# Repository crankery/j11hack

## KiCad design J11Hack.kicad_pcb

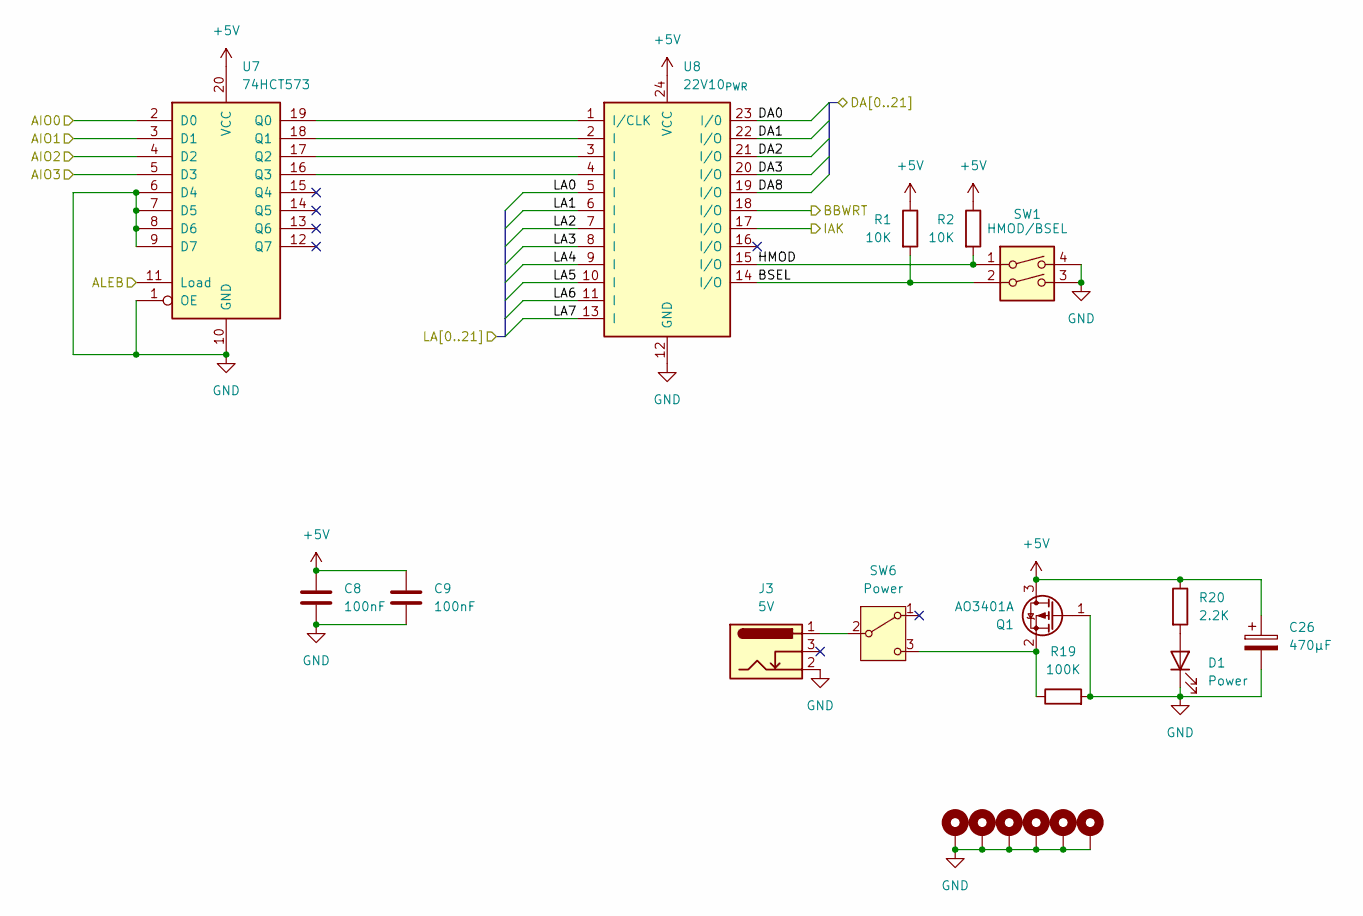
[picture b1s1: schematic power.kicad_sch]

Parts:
C8, C9: 100nF; C_Disc_D4.3mm_W1.9mm_P5.00mm
C26: 470µF; CP_Radial_D8.0mm_P3.50mm
D1: Power; LED_D3.0mm
H1, H2, H3, H4, H5, H6: MountingHole_Pad; MountingHole_2.7mm_M2.5_DIN965_Pad
J3: 5V; BarrelJack_Horizontal
Q1: AO3401A; SOT-23
R1, R2: 10K; R_Axial_DIN0207_L6.3mm_D2.5mm_P7.62mm_Horizontal
R19: 100K; R_Axial_DIN0207_L6.3mm_D2.5mm_P7.62mm_Horizontal
R20: 2.2K; R_Axial_DIN0207_L6.3mm_D2.5mm_P7.62mm_Horizontal
SW1: HMOD/BSEL; SW_DIP_SPSTx02_Slide_9.78x7.26mm_W7.62mm_P2.54mm
SW6: Power; SW_2AS1T2A1M6QES
U7: 74HCT573; DIP-20_W7.62mm_Socket
U8: 22V10_{PWR}; DIP-24_W7.62mm_Socket

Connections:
+5V: C8.1, C9.1, C26.1, Q1.3 (D), R1.1, R2.1, R20.1, U7.20 (VCC), U8.24 (VCC); also elsewhere on the board
/CPU/AIO0: U7.2 (D0); also elsewhere on the board
/CPU/AIO1: U7.3 (D1); also elsewhere on the board
/CPU/AIO2: U7.4 (D2); also elsewhere on the board
/CPU/AIO3: U7.5 (D3); also elsewhere on the board
/CPU/ALEB: U7.11 (Load); also elsewhere on the board
/CPU/BBWRT: U8.18 (I/O); also elsewhere on the board
/CPU/DA0: U8.23 (I/0); also elsewhere on the board
/CPU/DA1: U8.22 (I/O); also elsewhere on the board
/CPU/DA2: U8.21 (I/O); also elsewhere on the board
/CPU/DA3: U8.20 (I/O); also elsewhere on the board
/CPU/DA8: U8.19 (I/O); also elsewhere on the board
/CPU/LA0: U8.5 (I); also elsewhere on the board
/CPU/LA1: U8.6 (I); also elsewhere on the board
/CPU/LA2: U8.7 (I); also elsewhere on the board
/CPU/LA3: U8.8 (I); also elsewhere on the board
/CPU/LA4: U8.9 (I); also elsewhere on the board
/CPU/LA5: U8.10 (I); also elsewhere on the board
/CPU/LA6: U8.11 (I); also elsewhere on the board
/CPU/LA7: U8.13 (I); also elsewhere on the board
/Power/BSEL: R1.2, SW1.2, U8.14 (I/O)
/Power/HMOD: R2.2, SW1.1, U8.15 (I/O)
/Power/IAK: U8.17 (I/O)
GND: C8.2, C9.2, C26.2, D1.1 (K), H1.1 (1_1), H2.1 (1_1), H3.1 (1_1), H4.1 (1_1), H5.1 (1_1), H6.1 (1_1), J3.2, Q1.1 (G), R19.2, SW1.3, SW1.4, U7.1 (OE), U7.6 (D4), U7.7 (D5), U7.8 (D6), U7.9 (D7), U7.10 (GND), U8.12 (GND); also elsewhere on the board
unnamed: D1.2 (A), R20.2
unnamed: Q1.2 (S), R19.1, SW6.3 (C)
unnamed: J3.1, SW6.2 (B)
unnamed: U7.19 (Q0), U8.1 (I/CLK)
unnamed: U7.18 (Q1), U8.2 (I)
unnamed: U7.17 (Q2), U8.3 (I)
unnamed: U7.16 (Q3), U8.4 (I)

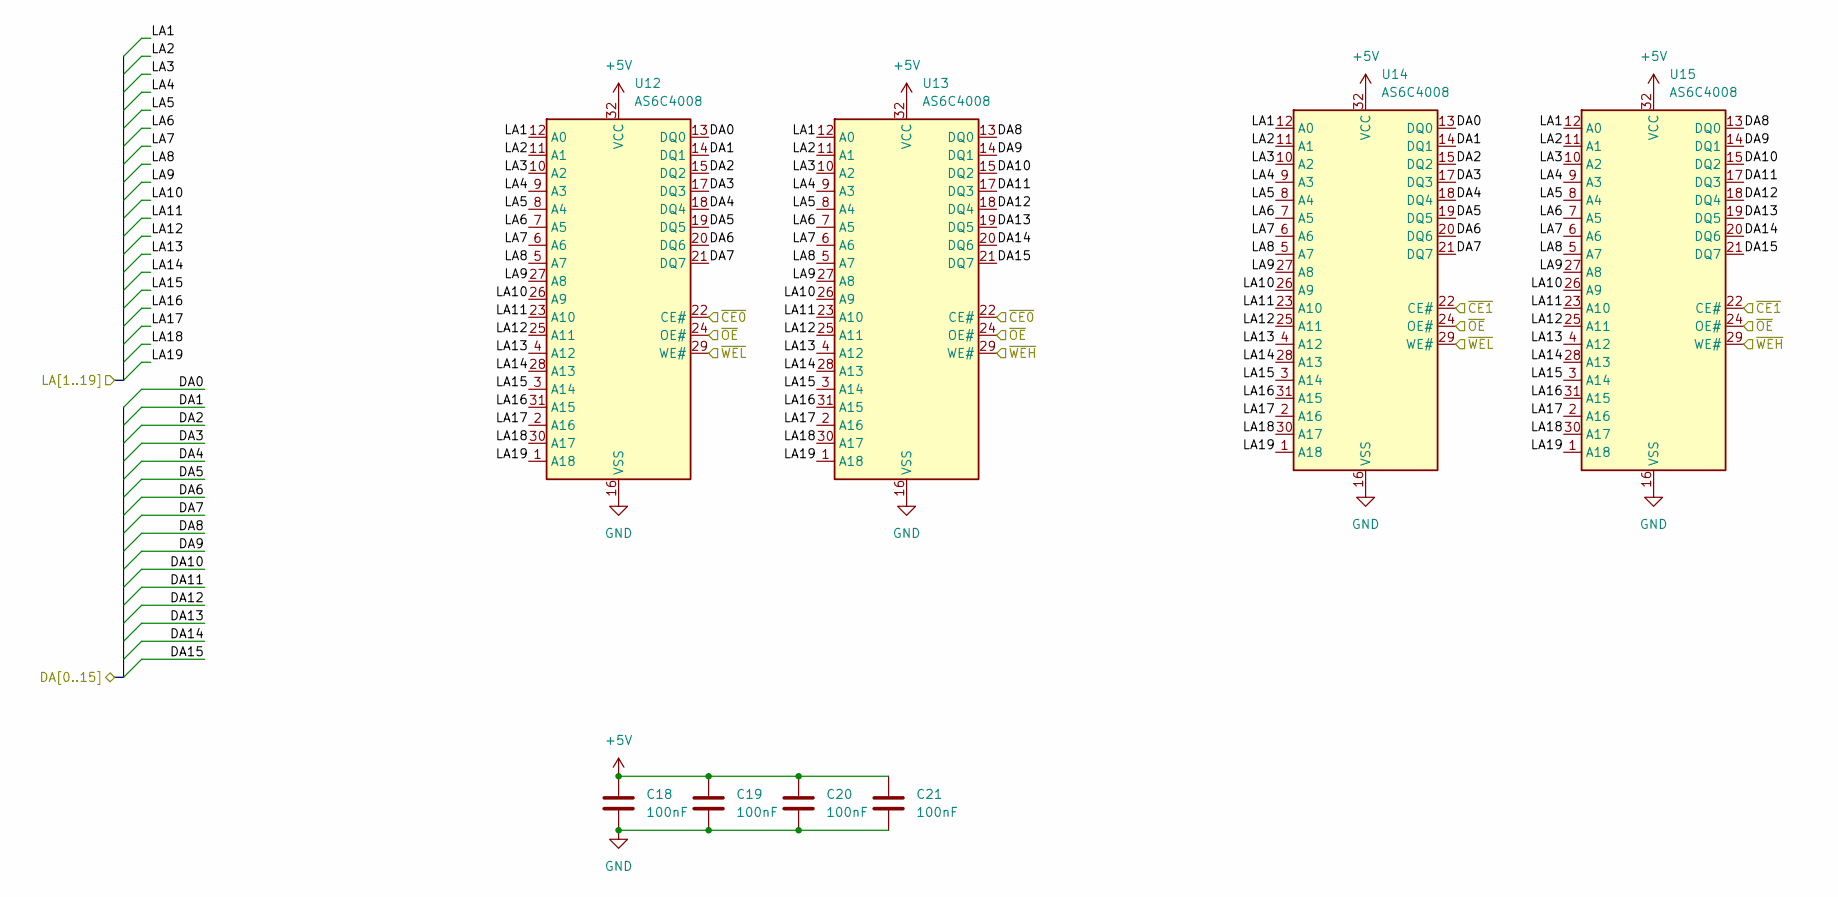
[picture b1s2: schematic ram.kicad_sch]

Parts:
C18, C19, C20, C21: 100nF; C_Disc_D4.3mm_W1.9mm_P5.00mm
U12, U13, U14, U15: AS6C4008; DIP-32_W15.24mm_Socket

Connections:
+5V: C18.1, C19.1, C20.1, C21.1, U12.32 (VCC), U13.32 (VCC), U14.32 (VCC), U15.32 (VCC); also elsewhere on the board
/CPU/DA0: U12.13 (DQ0), U14.13 (DQ0); also elsewhere on the board
/CPU/DA1: U12.14 (DQ1), U14.14 (DQ1); also elsewhere on the board
/CPU/DA2: U12.15 (DQ2), U14.15 (DQ2); also elsewhere on the board
/CPU/DA3: U12.17 (DQ3), U14.17 (DQ3); also elsewhere on the board
/CPU/DA4: U12.18 (DQ4), U14.18 (DQ4); also elsewhere on the board
/CPU/DA5: U12.19 (DQ5), U14.19 (DQ5); also elsewhere on the board
/CPU/DA6: U12.20 (DQ6), U14.20 (DQ6); also elsewhere on the board
/CPU/DA7: U12.21 (DQ7), U14.21 (DQ7); also elsewhere on the board
/CPU/DA8: U13.13 (DQ0), U15.13 (DQ0); also elsewhere on the board
/CPU/DA9: U13.14 (DQ1), U15.14 (DQ1); also elsewhere on the board
/CPU/DA10: U13.15 (DQ2), U15.15 (DQ2); also elsewhere on the board
/CPU/DA11: U13.17 (DQ3), U15.17 (DQ3); also elsewhere on the board
/CPU/DA12: U13.18 (DQ4), U15.18 (DQ4); also elsewhere on the board
/CPU/DA13: U13.19 (DQ5), U15.19 (DQ5); also elsewhere on the board
/CPU/DA14: U13.20 (DQ6), U15.20 (DQ6); also elsewhere on the board
/CPU/DA15: U13.21 (DQ7), U15.21 (DQ7); also elsewhere on the board
/CPU/LA0: U12.12 (A0), U13.12 (A0), U14.12 (A0), U15.12 (A0); also elsewhere on the board
/CPU/LA1: U12.11 (A1), U13.11 (A1), U14.11 (A1), U15.11 (A1); also elsewhere on the board
/CPU/LA2: U12.10 (A2), U13.10 (A2), U14.10 (A2), U15.10 (A2); also elsewhere on the board
/CPU/LA3: U12.9 (A3), U13.9 (A3), U14.9 (A3), U15.9 (A3); also elsewhere on the board
/CPU/LA4: U12.8 (A4), U13.8 (A4), U14.8 (A4), U15.8 (A4); also elsewhere on the board
/CPU/LA5: U12.7 (A5), U13.7 (A5), U14.7 (A5), U15.7 (A5); also elsewhere on the board
/CPU/LA6: U12.6 (A6), U13.6 (A6), U14.6 (A6), U15.6 (A6); also elsewhere on the board
/CPU/LA7: U12.5 (A7), U13.5 (A7), U14.5 (A7), U15.5 (A7); also elsewhere on the board
/CPU/LA8: U12.27 (A8), U13.27 (A8), U14.27 (A8), U15.27 (A8); also elsewhere on the board
/CPU/LA9: U12.26 (A9), U13.26 (A9), U14.26 (A9), U15.26 (A9); also elsewhere on the board
/CPU/LA10: U12.23 (A10), U13.23 (A10), U14.23 (A10), U15.23 (A10); also elsewhere on the board
/CPU/LA11: U12.25 (A11), U13.25 (A11), U14.25 (A11), U15.25 (A11); also elsewhere on the board
/CPU/LA12: U12.4 (A12), U13.4 (A12), U14.4 (A12), U15.4 (A12); also elsewhere on the board
/CPU/LA13: U12.28 (A13), U13.28 (A13), U14.28 (A13), U15.28 (A13); also elsewhere on the board
/CPU/LA14: U12.3 (A14), U13.3 (A14), U14.3 (A14), U15.3 (A14); also elsewhere on the board
/CPU/LA15: U12.31 (A15), U13.31 (A15), U14.31 (A15), U15.31 (A15); also elsewhere on the board
/CPU/LA16: U12.2 (A16), U13.2 (A16), U14.2 (A16), U15.2 (A16); also elsewhere on the board
/CPU/LA17: U12.30 (A17), U13.30 (A17), U14.30 (A17), U15.30 (A17); also elsewhere on the board
/CPU/LA18: U12.1 (A18), U13.1 (A18), U14.1 (A18), U15.1 (A18); also elsewhere on the board
/CPU/~CE0: U12.22 (CE#), U13.22 (CE#); also elsewhere on the board
/CPU/~CE1: U14.22 (CE#), U15.22 (CE#); also elsewhere on the board
/CPU/~OE: U12.24 (OE#), U13.24 (OE#), U14.24 (OE#), U15.24 (OE#); also elsewhere on the board
/CPU/~WEH: U13.29 (WE#), U15.29 (WE#); also elsewhere on the board
/CPU/~WEL: U12.29 (WE#), U14.29 (WE#); also elsewhere on the board
GND: C18.2, C19.2, C20.2, C21.2, U12.16 (VSS), U13.16 (VSS), U14.16 (VSS), U15.16 (VSS); also elsewhere on the board

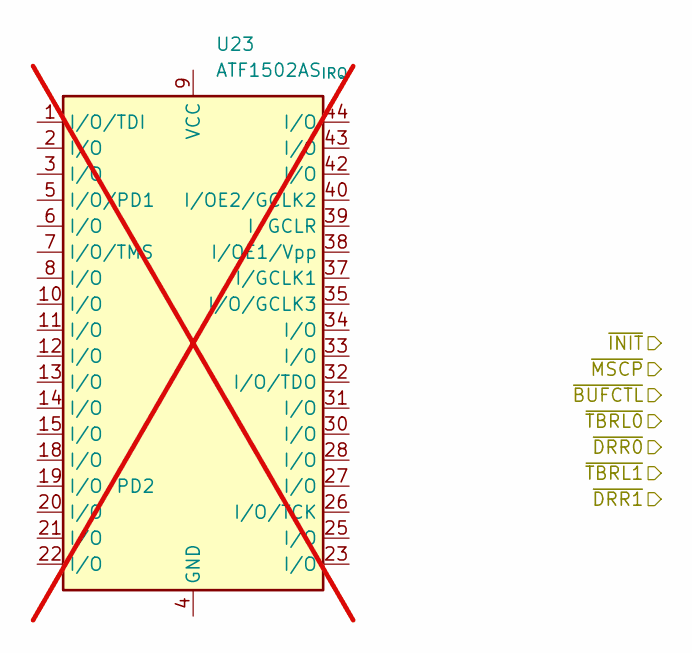
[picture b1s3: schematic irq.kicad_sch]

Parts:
U23: ATF1502AS_{IRQ}; TQFP-44_10x10mm_P0.8mm; not fitted

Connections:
unnamed: U23.4 (GND), U23.16 (GND), U23.24 (GND), U23.36 (GND)
unnamed: U23.9 (VCC), U23.17 (VCC), U23.29 (VCC), U23.41 (VCC)

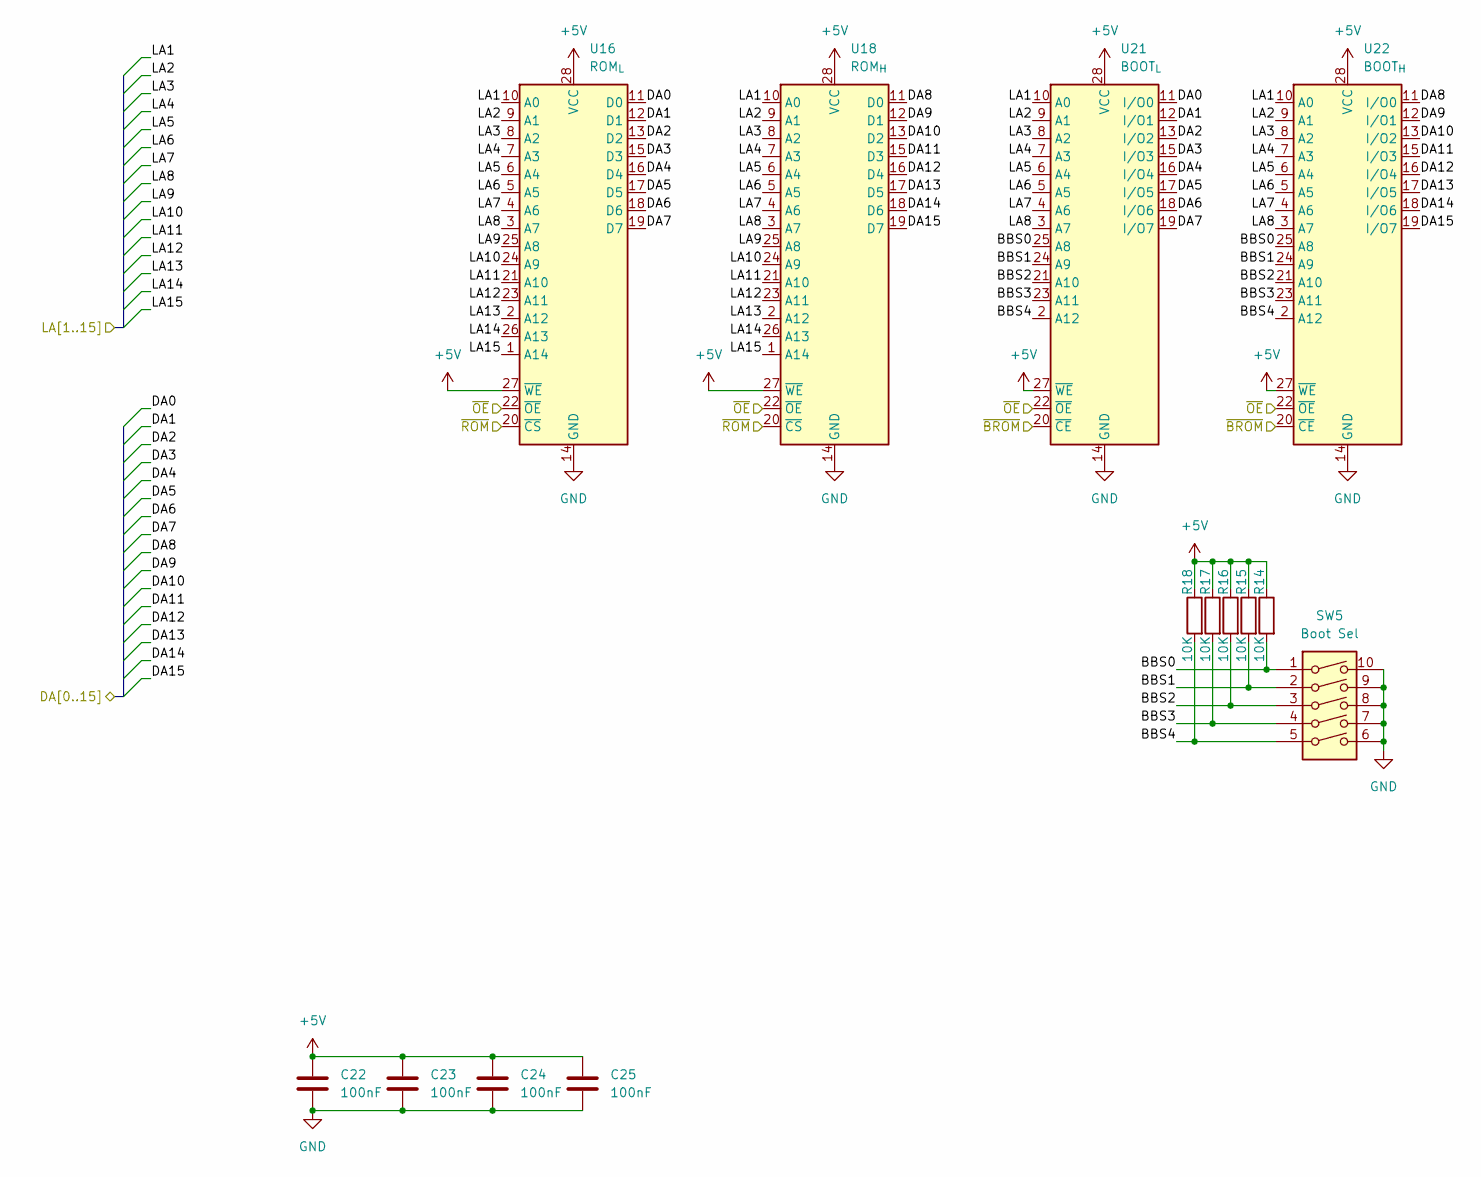
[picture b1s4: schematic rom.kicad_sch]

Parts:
C22, C23, C24, C25: 100nF; C_Disc_D4.3mm_W1.9mm_P5.00mm
R14, R15, R16, R17, R18: 10K; R_Axial_DIN0207_L6.3mm_D2.5mm_P7.62mm_Horizontal
SW5: Boot Sel; SW_DIP_SPSTx05_Slide_9.78x14.88mm_W7.62mm_P2.54mm
U16: ROM_{L}; DIP-28_W15.24mm_Socket
U18: ROM_{H}; DIP-28_W15.24mm_Socket
U21: BOOT_{L}; DIP-28_W15.24mm_Socket
U22: BOOT_{H}; DIP-28_W15.24mm_Socket

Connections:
+5V: C22.1, C23.1, C24.1, C25.1, R14.1, R15.1, R16.1, R17.1, R18.1, U16.27 (~WE), U16.28 (VCC), U18.27 (~WE), U18.28 (VCC), U21.27 (~WE), U21.28 (VCC), U22.27 (~WE), U22.28 (VCC); also elsewhere on the board
/CPU/DA0: U16.11 (D0), U21.11 (I/O0); also elsewhere on the board
/CPU/DA1: U16.12 (D1), U21.12 (I/O1); also elsewhere on the board
/CPU/DA2: U16.13 (D2), U21.13 (I/O2); also elsewhere on the board
/CPU/DA3: U16.15 (D3), U21.15 (I/O3); also elsewhere on the board
/CPU/DA4: U16.16 (D4), U21.16 (I/O4); also elsewhere on the board
/CPU/DA5: U16.17 (D5), U21.17 (I/O5); also elsewhere on the board
/CPU/DA6: U16.18 (D6), U21.18 (I/O6); also elsewhere on the board
/CPU/DA7: U16.19 (D7), U21.19 (I/O7); also elsewhere on the board
/CPU/DA8: U18.11 (D0), U22.11 (I/O0); also elsewhere on the board
/CPU/DA9: U18.12 (D1), U22.12 (I/O1); also elsewhere on the board
/CPU/DA10: U18.13 (D2), U22.13 (I/O2); also elsewhere on the board
/CPU/DA11: U18.15 (D3), U22.15 (I/O3); also elsewhere on the board
/CPU/DA12: U18.16 (D4), U22.16 (I/O4); also elsewhere on the board
/CPU/DA13: U18.17 (D5), U22.17 (I/O5); also elsewhere on the board
/CPU/DA14: U18.18 (D6), U22.18 (I/O6); also elsewhere on the board
/CPU/DA15: U18.19 (D7), U22.19 (I/O7); also elsewhere on the board
/CPU/LA0: U16.10 (A0), U18.10 (A0), U21.10 (A0), U22.10 (A0); also elsewhere on the board
/CPU/LA1: U16.9 (A1), U18.9 (A1), U21.9 (A1), U22.9 (A1); also elsewhere on the board
/CPU/LA2: U16.8 (A2), U18.8 (A2), U21.8 (A2), U22.8 (A2); also elsewhere on the board
/CPU/LA3: U16.7 (A3), U18.7 (A3), U21.7 (A3), U22.7 (A3); also elsewhere on the board
/CPU/LA4: U16.6 (A4), U18.6 (A4), U21.6 (A4), U22.6 (A4); also elsewhere on the board
/CPU/LA5: U16.5 (A5), U18.5 (A5), U21.5 (A5), U22.5 (A5); also elsewhere on the board
/CPU/LA6: U16.4 (A6), U18.4 (A6), U21.4 (A6), U22.4 (A6); also elsewhere on the board
/CPU/LA7: U16.3 (A7), U18.3 (A7), U21.3 (A7), U22.3 (A7); also elsewhere on the board
/CPU/LA8: U16.25 (A8), U18.25 (A8); also elsewhere on the board
/CPU/LA9: U16.24 (A9), U18.24 (A9); also elsewhere on the board
/CPU/LA10: U16.21 (A10), U18.21 (A10); also elsewhere on the board
/CPU/LA11: U16.23 (A11), U18.23 (A11); also elsewhere on the board
/CPU/LA12: U16.2 (A12), U18.2 (A12); also elsewhere on the board
/CPU/LA13: U16.26 (A13), U18.26 (A13); also elsewhere on the board
/CPU/LA14: U16.1 (A14), U18.1 (A14); also elsewhere on the board
/CPU/~BROM: U21.20 (~CE), U22.20 (~CE); also elsewhere on the board
/CPU/~OE: U16.22 (~OE), U18.22 (~OE), U21.22 (~OE), U22.22 (~OE); also elsewhere on the board
/CPU/~ROM: U16.20 (~CS), U18.20 (~CS); also elsewhere on the board
/ROM/BBS0: R14.2, SW5.1, U21.25 (A8), U22.25 (A8)
/ROM/BBS1: R15.2, SW5.2, U21.24 (A9), U22.24 (A9)
/ROM/BBS2: R16.2, SW5.3, U21.21 (A10), U22.21 (A10)
/ROM/BBS3: R17.2, SW5.4, U21.23 (A11), U22.23 (A11)
/ROM/BBS4: R18.2, SW5.5, U21.2 (A12), U22.2 (A12)
GND: C22.2, C23.2, C24.2, C25.2, SW5.6, SW5.7, SW5.8, SW5.9, SW5.10, U16.14 (GND), U18.14 (GND), U21.14 (GND), U22.14 (GND); also elsewhere on the board

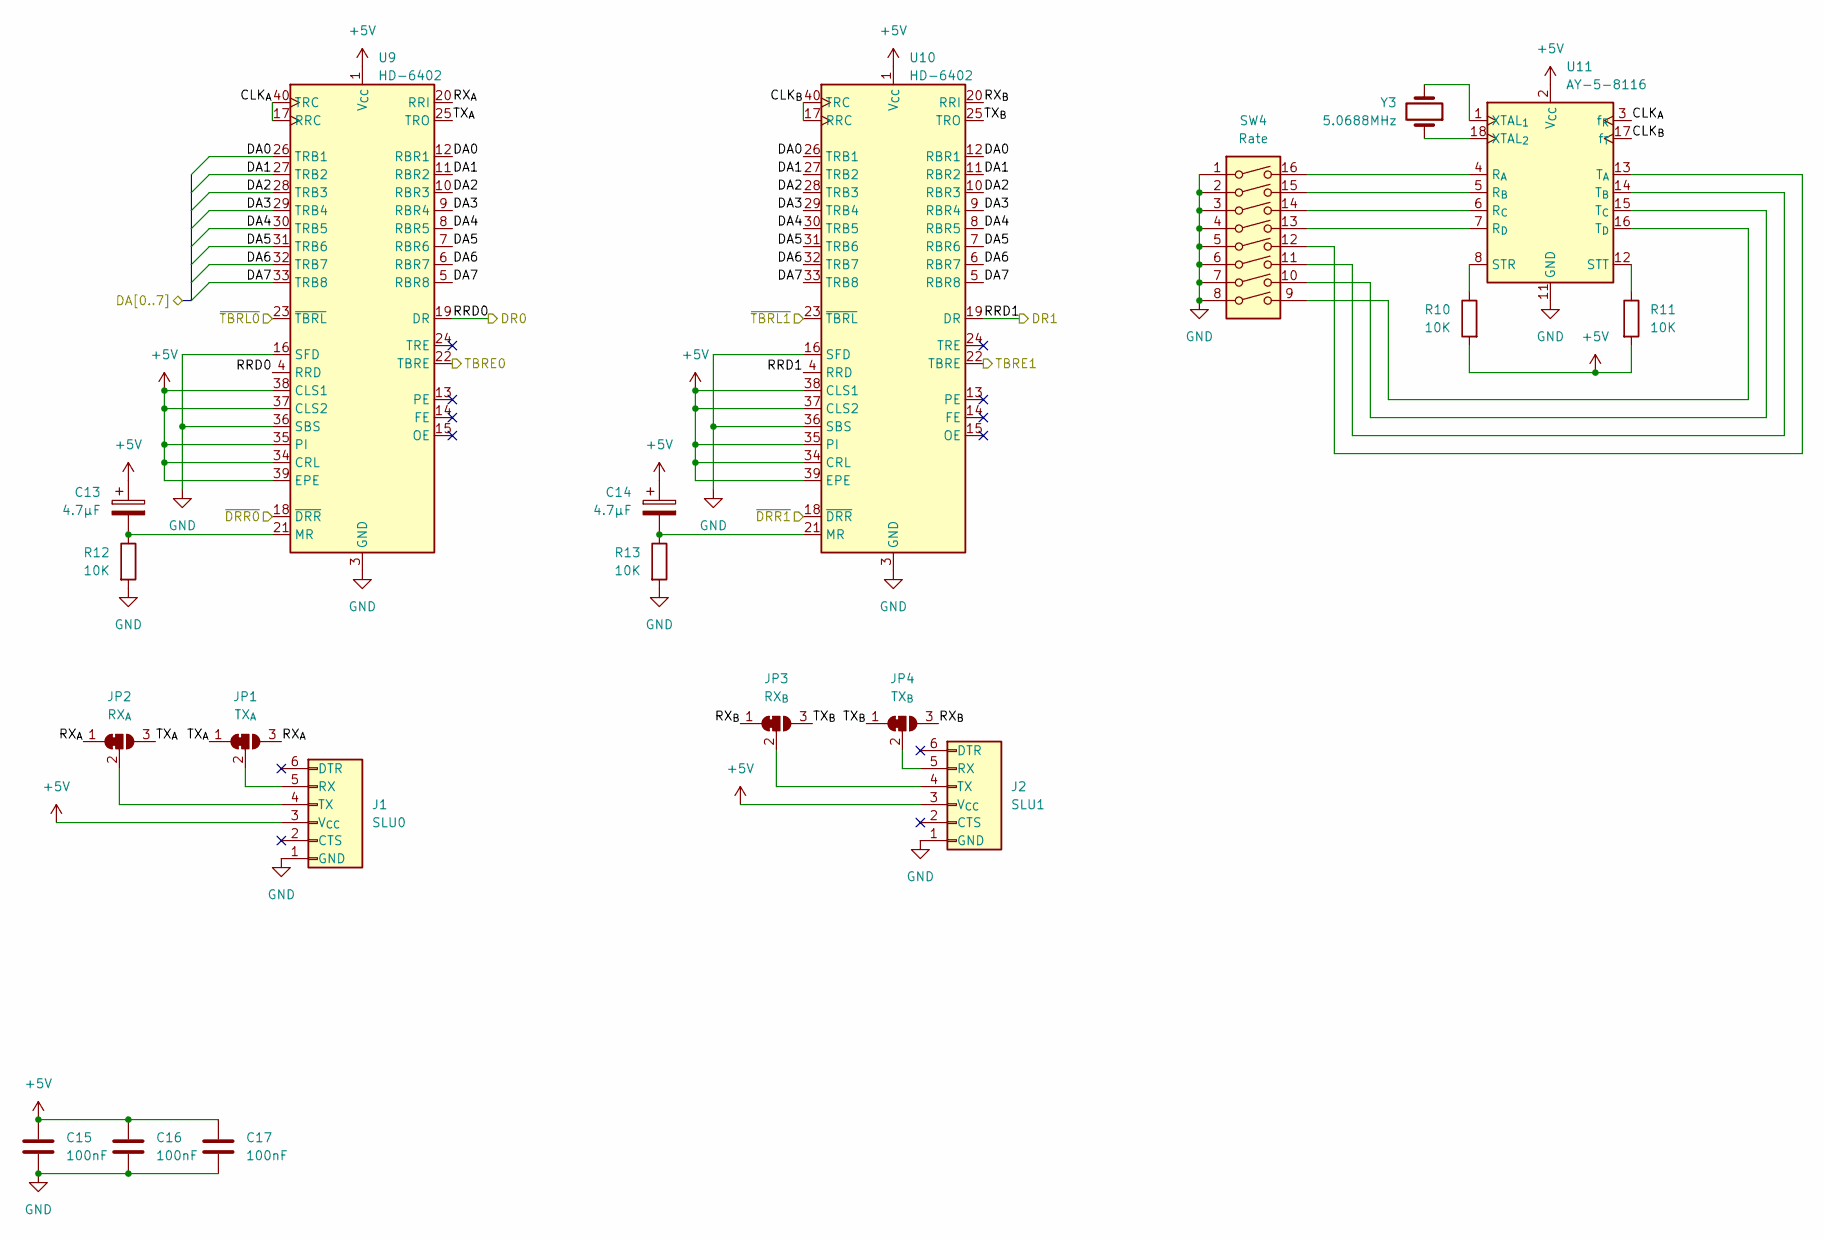
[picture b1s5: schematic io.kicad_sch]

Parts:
C13, C14: 4.7µF; CP_Radial_D5.0mm_P2.00mm
C15, C16, C17: 100nF; C_Disc_D4.3mm_W1.9mm_P5.00mm
J1: SLU0; PinSocket_1x06_P2.54mm_Horizontal
J2: SLU1; PinSocket_1x06_P2.54mm_Horizontal
JP1: TX_{A}; SolderJumper-3_P1.3mm_Bridged12_RoundedPad1.0x1.5mm
JP2: RX_{A}; SolderJumper-3_P1.3mm_Bridged12_RoundedPad1.0x1.5mm
JP3: RX_{B}; SolderJumper-3_P1.3mm_Bridged12_RoundedPad1.0x1.5mm
JP4: TX_{B}; SolderJumper-3_P1.3mm_Bridged12_RoundedPad1.0x1.5mm
R10, R11, R12, R13: 10K; R_Axial_DIN0207_L6.3mm_D2.5mm_P7.62mm_Horizontal
SW4: Rate; SW_DIP_SPSTx08_Slide_9.78x22.5mm_W7.62mm_P2.54mm
U9, U10: HD-6402; DIP-40_W15.24mm_Socket
U11: AY-5-8116; DIP-18_W7.62mm_Socket
Y3: 5.0688MHz; Crystal_HC49-U_Vertical

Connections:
+5V: C13.1, C14.1, C15.1, C16.1, C17.1, J1.3 (V_{CC}), J2.3 (V_{CC}), R10.2, R11.2, U9.1 (V_{CC}), U9.34 (CRL), U9.35 (PI), U9.37 (CLS2), U9.38 (CLS1), U9.39 (EPE), U10.1 (V_{CC}), U10.34 (CRL), U10.35 (PI), U10.37 (CLS2), U10.38 (CLS1), U10.39 (EPE), U11.2 (V_{CC}); also elsewhere on the board
/CPU/DA0: U9.12 (RBR1), U9.26 (TRB1), U10.12 (RBR1), U10.26 (TRB1); also elsewhere on the board
/CPU/DA1: U9.11 (RBR2), U9.27 (TRB2), U10.11 (RBR2), U10.27 (TRB2); also elsewhere on the board
/CPU/DA2: U9.10 (RBR3), U9.28 (TRB3), U10.10 (RBR3), U10.28 (TRB3); also elsewhere on the board
/CPU/DA3: U9.9 (RBR4), U9.29 (TRB4), U10.9 (RBR4), U10.29 (TRB4); also elsewhere on the board
/CPU/DA4: U9.8 (RBR5), U9.30 (TRB5), U10.8 (RBR5), U10.30 (TRB5); also elsewhere on the board
/CPU/DA5: U9.7 (RBR6), U9.31 (TRB6), U10.7 (RBR6), U10.31 (TRB6); also elsewhere on the board
/CPU/DA6: U9.6 (RBR7), U9.32 (TRB7), U10.6 (RBR7), U10.32 (TRB7); also elsewhere on the board
/CPU/DA7: U9.5 (RBR8), U9.33 (TRB8), U10.5 (RBR8), U10.33 (TRB8); also elsewhere on the board
/CPU/TBRE0: U9.22 (TBRE); also elsewhere on the board
/CPU/TBRE1: U10.22 (TBRE); also elsewhere on the board
/CPU/~DRR0: U9.18 (~DRR); also elsewhere on the board
/CPU/~DRR1: U10.18 (~DRR); also elsewhere on the board
/CPU/~TBRL0: U9.23 (~TBRL); also elsewhere on the board
/CPU/~TBRL1: U10.23 (~TBRL); also elsewhere on the board
/IO/CLK_{A}: U9.17 (RRC), U9.40 (TRC), U11.3 (f_{R})
/IO/CLK_{B}: U10.17 (RRC), U10.40 (TRC), U11.17 (f_{T})
/IO/RRD0: U9.4 (RRD), U9.19 (DR); also elsewhere on the board
/IO/RRD1: U10.4 (RRD), U10.19 (DR); also elsewhere on the board
/IO/RX_{A}: JP1.3 (B), JP2.1 (A), U9.20 (RRI)
/IO/RX_{B}: JP3.1 (A), JP4.3 (B), U10.20 (RRI)
/IO/TX_{A}: JP1.1 (A), JP2.3 (B), U9.25 (TRO)
/IO/TX_{B}: JP3.3 (B), JP4.1 (A), U10.25 (TRO)
GND: C15.2, C16.2, C17.2, J1.1 (GND), J2.1 (GND), R12.2, R13.2, SW4.1, SW4.2, SW4.3, SW4.4, SW4.5, SW4.6, SW4.7, SW4.8, U9.3 (GND), U9.16 (SFD), U9.36 (SBS), U10.3 (GND), U10.16 (SFD), U10.36 (SBS), U11.11 (GND); also elsewhere on the board
unnamed: J1.5 (RX), JP1.2 (C)
unnamed: J1.4 (TX), JP2.2 (C)
unnamed: J2.5 (RX), JP4.2 (C)
unnamed: J2.4 (TX), JP3.2 (C)
unnamed: C13.2, R12.1, U9.21 (MR)
unnamed: C14.2, R13.1, U10.21 (MR)
unnamed: SW4.16, U11.4 (R_{A})
unnamed: SW4.15, U11.5 (R_{B})
unnamed: SW4.14, U11.6 (R_{C})
unnamed: SW4.13, U11.7 (R_{D})
unnamed: R10.1, U11.8 (STR)
unnamed: R11.1, U11.12 (STT)
unnamed: SW4.12, U11.13 (T_{A})
unnamed: SW4.11, U11.14 (T_{B})
unnamed: SW4.10, U11.15 (T_{C})
unnamed: SW4.9, U11.16 (T_{D})
unnamed: U11.1 (XTAL_{1}), Y3.2
unnamed: U11.18 (XTAL_{2}), Y3.1

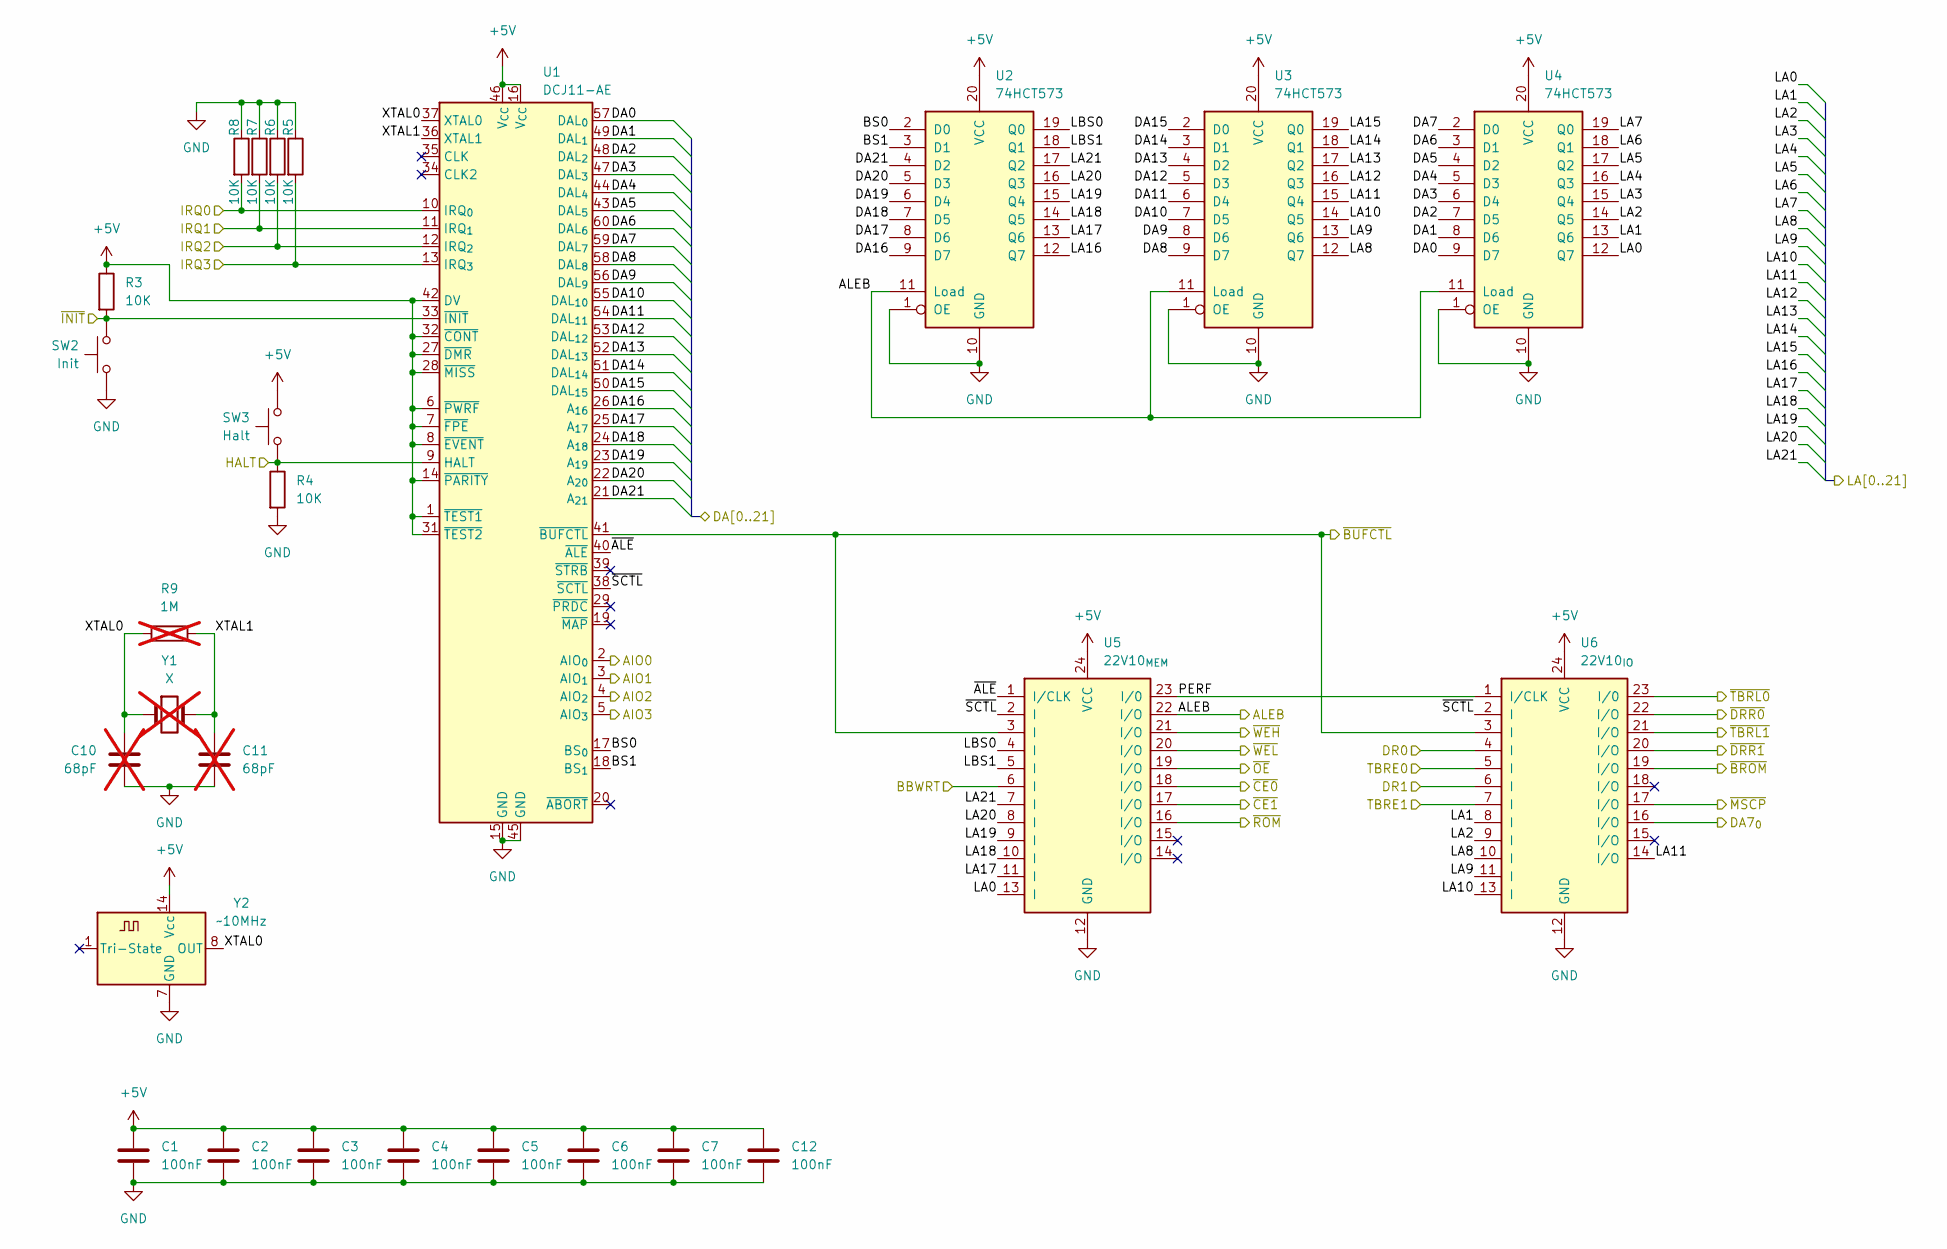
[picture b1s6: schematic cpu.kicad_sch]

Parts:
C1, C2, C3, C4, C5, C6, C7, C12: 100nF; C_Disc_D4.3mm_W1.9mm_P5.00mm
C10, C11: 68pF; C_Disc_D4.3mm_W1.9mm_P5.00mm; not fitted
R3, R4, R5, R6, R7, R8: 10K; R_Axial_DIN0207_L6.3mm_D2.5mm_P7.62mm_Horizontal
R9: 1M; R_Axial_DIN0207_L6.3mm_D2.5mm_P7.62mm_Horizontal; not fitted
SW2: Init; SW_Tactile_SPST_Angled_PTS645Vx58-2LFS
SW3: Halt; SW_Tactile_SPST_Angled_PTS645Vx58-2LFS
U1: DCJ11-AE; DIP-60
U2, U3, U4: 74HCT573; DIP-20_W7.62mm_Socket
U5: 22V10_{MEM}; DIP-24_W7.62mm_Socket
U6: 22V10_{IO}; DIP-24_W7.62mm_Socket
Y1: X; Crystal_HC49-U_Vertical; not fitted
Y2: ~10MHz; Oscillator_DIP-14

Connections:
+5V: C1.1, C2.1, C3.1, C4.1, C5.1, C6.1, C7.1, C12.1, R3.1, SW3.2, U1.1 (~TEST1), U1.6 (~PWRF), U1.7 (~FPE), U1.8 (~EVENT), U1.14 (~PARITY), U1.16 (V_{CC}), U1.27 (~DMR), U1.28 (~MISS), U1.31 (~TEST2), U1.32 (~CONT), U1.42 (DV), U1.46 (V_{CC}), U2.20 (VCC), U3.20 (VCC), U4.20 (VCC), U5.24 (VCC), U6.24 (VCC), Y2.14 (Vcc); also elsewhere on the board
/CPU/AIO0: U1.2 (AIO_{0}); also elsewhere on the board
/CPU/AIO1: U1.3 (AIO_{1}); also elsewhere on the board
/CPU/AIO2: U1.4 (AIO_{2}); also elsewhere on the board
/CPU/AIO3: U1.5 (AIO_{3}); also elsewhere on the board
/CPU/ALEB: U2.11 (Load), U3.11 (Load), U4.11 (Load), U5.22 (I/O); also elsewhere on the board
/CPU/BBWRT: U5.6 (I); also elsewhere on the board
/CPU/BS0: U1.17 (BS_{0}), U2.2 (D0)
/CPU/BS1: U1.18 (BS_{1}), U2.3 (D1)
/CPU/DA0: U1.57 (DAL_{0}), U4.9 (D7); also elsewhere on the board
/CPU/DA1: U1.49 (DAL_{1}), U4.8 (D6); also elsewhere on the board
/CPU/DA2: U1.48 (DAL_{2}), U4.7 (D5); also elsewhere on the board
/CPU/DA3: U1.47 (DAL_{3}), U4.6 (D4); also elsewhere on the board
/CPU/DA4: U1.44 (DAL_{4}), U4.5 (D3); also elsewhere on the board
/CPU/DA5: U1.43 (DAL_{5}), U4.4 (D2); also elsewhere on the board
/CPU/DA6: U1.60 (DAL_{6}), U4.3 (D1); also elsewhere on the board
/CPU/DA7: U1.59 (DAL_{7}), U4.2 (D0); also elsewhere on the board
/CPU/DA7_{0}: U6.16 (I/O)
/CPU/DA8: U1.58 (DAL_{8}), U3.9 (D7); also elsewhere on the board
/CPU/DA9: U1.56 (DAL_{9}), U3.8 (D6); also elsewhere on the board
/CPU/DA10: U1.55 (DAL_{10}), U3.7 (D5); also elsewhere on the board
/CPU/DA11: U1.54 (DAL_{11}), U3.6 (D4); also elsewhere on the board
/CPU/DA12: U1.53 (DAL_{12}), U3.5 (D3); also elsewhere on the board
/CPU/DA13: U1.52 (DAL_{13}), U3.4 (D2); also elsewhere on the board
/CPU/DA14: U1.51 (DAL_{14}), U3.3 (D1); also elsewhere on the board
/CPU/DA15: U1.50 (DAL_{15}), U3.2 (D0); also elsewhere on the board
/CPU/DA16: U1.26 (A_{16}), U2.9 (D7)
/CPU/DA17: U1.25 (A_{17}), U2.8 (D6)
/CPU/DA18: U1.24 (A_{18}), U2.7 (D5)
/CPU/DA19: U1.23 (A_{19}), U2.6 (D4)
/CPU/DA20: U1.22 (A_{20}), U2.5 (D3)
/CPU/DA21: U1.21 (A_{21}), U2.4 (D2)
/CPU/HALT: R4.1, SW3.1, U1.9 (HALT)
/CPU/IRQ0: R8.2, U1.10 (IRQ_{0})
/CPU/IRQ1: R7.2, U1.11 (IRQ_{1})
/CPU/IRQ2: R6.2, U1.12 (IRQ_{2})
/CPU/IRQ3: R5.2, U1.13 (IRQ_{3})
/CPU/LA0: U4.12 (Q7), U5.13 (I); also elsewhere on the board
/CPU/LA1: U4.13 (Q6), U6.8 (I); also elsewhere on the board
/CPU/LA2: U4.14 (Q5), U6.9 (I); also elsewhere on the board
/CPU/LA3: U4.15 (Q4); also elsewhere on the board
/CPU/LA4: U4.16 (Q3); also elsewhere on the board
/CPU/LA5: U4.17 (Q2); also elsewhere on the board
/CPU/LA6: U4.18 (Q1); also elsewhere on the board
/CPU/LA7: U4.19 (Q0); also elsewhere on the board
/CPU/LA8: U3.12 (Q7), U6.10 (I); also elsewhere on the board
/CPU/LA9: U3.13 (Q6), U6.11 (I); also elsewhere on the board
/CPU/LA10: U3.14 (Q5), U6.13 (I); also elsewhere on the board
/CPU/LA11: U3.15 (Q4), U6.14 (I/O); also elsewhere on the board
/CPU/LA12: U3.16 (Q3); also elsewhere on the board
/CPU/LA13: U3.17 (Q2); also elsewhere on the board
/CPU/LA14: U3.18 (Q1); also elsewhere on the board
/CPU/LA15: U3.19 (Q0); also elsewhere on the board
/CPU/LA16: U2.12 (Q7); also elsewhere on the board
/CPU/LA17: U2.13 (Q6), U5.11 (I); also elsewhere on the board
/CPU/LA18: U2.14 (Q5), U5.10 (I); also elsewhere on the board
/CPU/LA19: U2.15 (Q4), U5.9 (I)
/CPU/LA20: U2.16 (Q3), U5.8 (I)
/CPU/LA21: U2.17 (Q2), U5.7 (I)
/CPU/LBS0: U2.19 (Q0), U5.4 (I)
/CPU/LBS1: U2.18 (Q1), U5.5 (I)
/CPU/PERF: U5.23 (I/0), U6.1 (I/CLK)
/CPU/TBRE0: U6.5 (I); also elsewhere on the board
/CPU/TBRE1: U6.7 (I); also elsewhere on the board
/CPU/XTAL0: C10.1, R9.1, U1.37 (XTAL0), Y1.1, Y2.8 (OUT)
/CPU/XTAL1: C11.1, R9.2, U1.36 (XTAL1), Y1.2
/CPU/~ALE: U1.40 (~ALE), U5.1 (I/CLK)
/CPU/~BROM: U6.19 (I/O); also elsewhere on the board
/CPU/~BUFCTL: U1.41 (~BUFCTL), U5.3 (I), U6.3 (I)
/CPU/~CE0: U5.18 (I/O); also elsewhere on the board
/CPU/~CE1: U5.17 (I/O); also elsewhere on the board
/CPU/~DRR0: U6.22 (I/O); also elsewhere on the board
/CPU/~DRR1: U6.20 (I/O); also elsewhere on the board
/CPU/~INIT: R3.2, SW2.2, U1.33 (~INIT)
/CPU/~MSCP: U6.17 (I/O)
/CPU/~OE: U5.19 (I/O); also elsewhere on the board
/CPU/~ROM: U5.16 (I/O); also elsewhere on the board
/CPU/~SCTL: U1.38 (~SCTL), U5.2 (I), U6.2 (I)
/CPU/~TBRL0: U6.23 (I/0); also elsewhere on the board
/CPU/~TBRL1: U6.21 (I/O); also elsewhere on the board
/CPU/~WEH: U5.21 (I/O); also elsewhere on the board
/CPU/~WEL: U5.20 (I/O); also elsewhere on the board
/IO/RRD0: U6.4 (I); also elsewhere on the board
/IO/RRD1: U6.6 (I); also elsewhere on the board
GND: C1.2, C2.2, C3.2, C4.2, C5.2, C6.2, C7.2, C10.2, C11.2, C12.2, R4.2, R5.1, R6.1, R7.1, R8.1, SW2.1, U1.15 (GND), U1.45 (GND), U2.1 (OE), U2.10 (GND), U3.1 (OE), U3.10 (GND), U4.1 (OE), U4.10 (GND), U5.12 (GND), U6.12 (GND), Y2.7 (GND); also elsewhere on the board

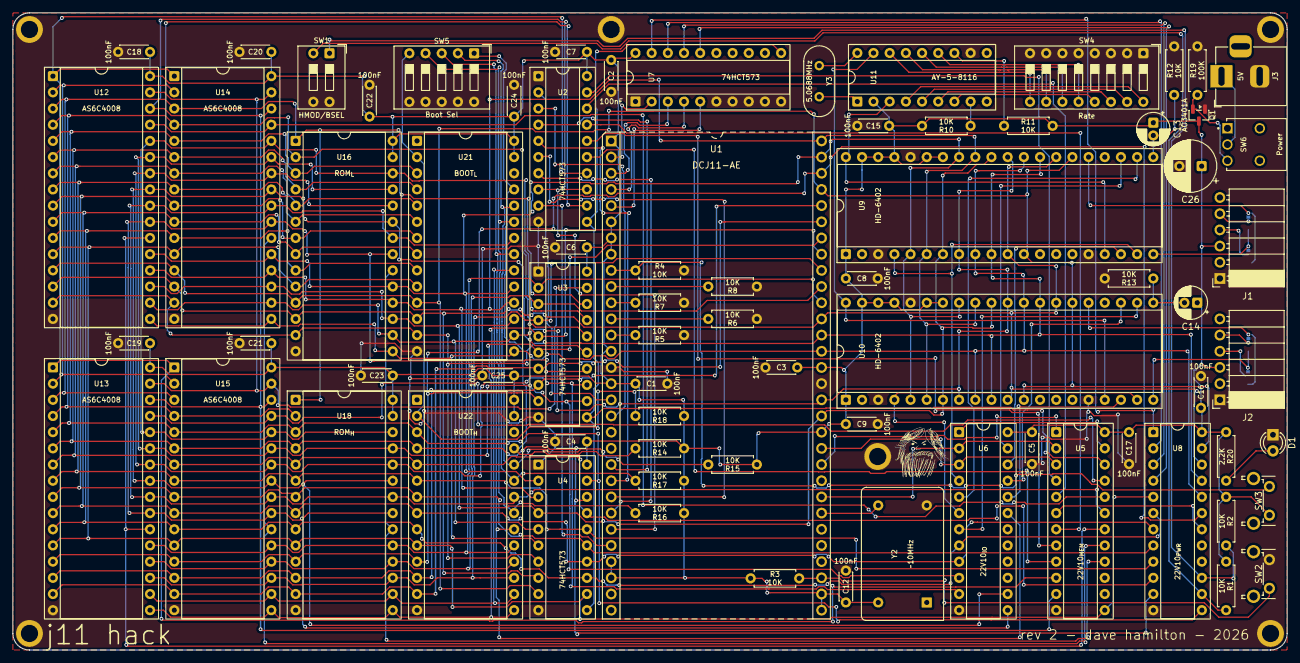
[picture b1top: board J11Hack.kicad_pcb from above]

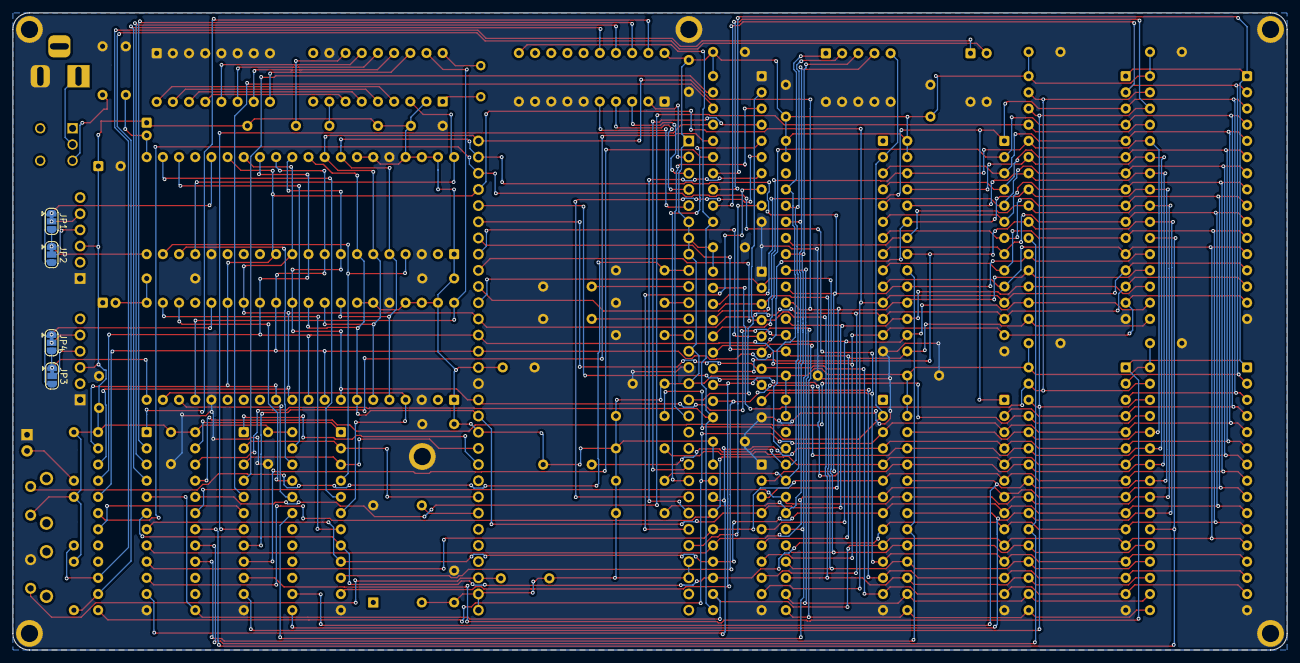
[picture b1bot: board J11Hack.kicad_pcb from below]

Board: 2 copper layers, 200.0 x 100.0 mm, 85 parts (4 on the bottom side), 120 nets.
